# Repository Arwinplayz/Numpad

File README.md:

# Arwin's Numpad
A custom NumPad designed and built using **KiCad** for PCB design and **Fusion 360** for 3D modeling. This is my first hackpad project.

## Description
This project is a fully custom NumPad. The PCB and schematic are designed in KiCad, and the case and parts are modeled in Fusion 360. 

## Screenshots

### Overall Hackpad

### Schematic

### PCB Layout 

### Case

## Bill of Materials (BOM)
| Part | Quantity | Description |
|------|---------|-------------|
| Mechanical switches | 16 | Standard MX-compatible switches |
| Keycaps | 16 | Cherry-style keycaps |
| Xiao RP2040 | 1 | Microcontroller |
| 0.91 inch OLED Screen | 1 | Screen |
| Rotary Encoder | 2 | Dials |
| PCB | 1 | Custom-designed PCB |
| Screws / Standoffs | 8 | For case assembly |
| Heatset inserts| 8 | For case assembly |
| Case | 1 | 3D printed |

## Usage / Assembly
1. Fabricate the PCB according to the KiCad files.  
2. Solder everything onto the PCB.  
3. 3D Print the case and fit the PCB inside.  
4. Connect the microcontroller to your computer via USB and test functionality.

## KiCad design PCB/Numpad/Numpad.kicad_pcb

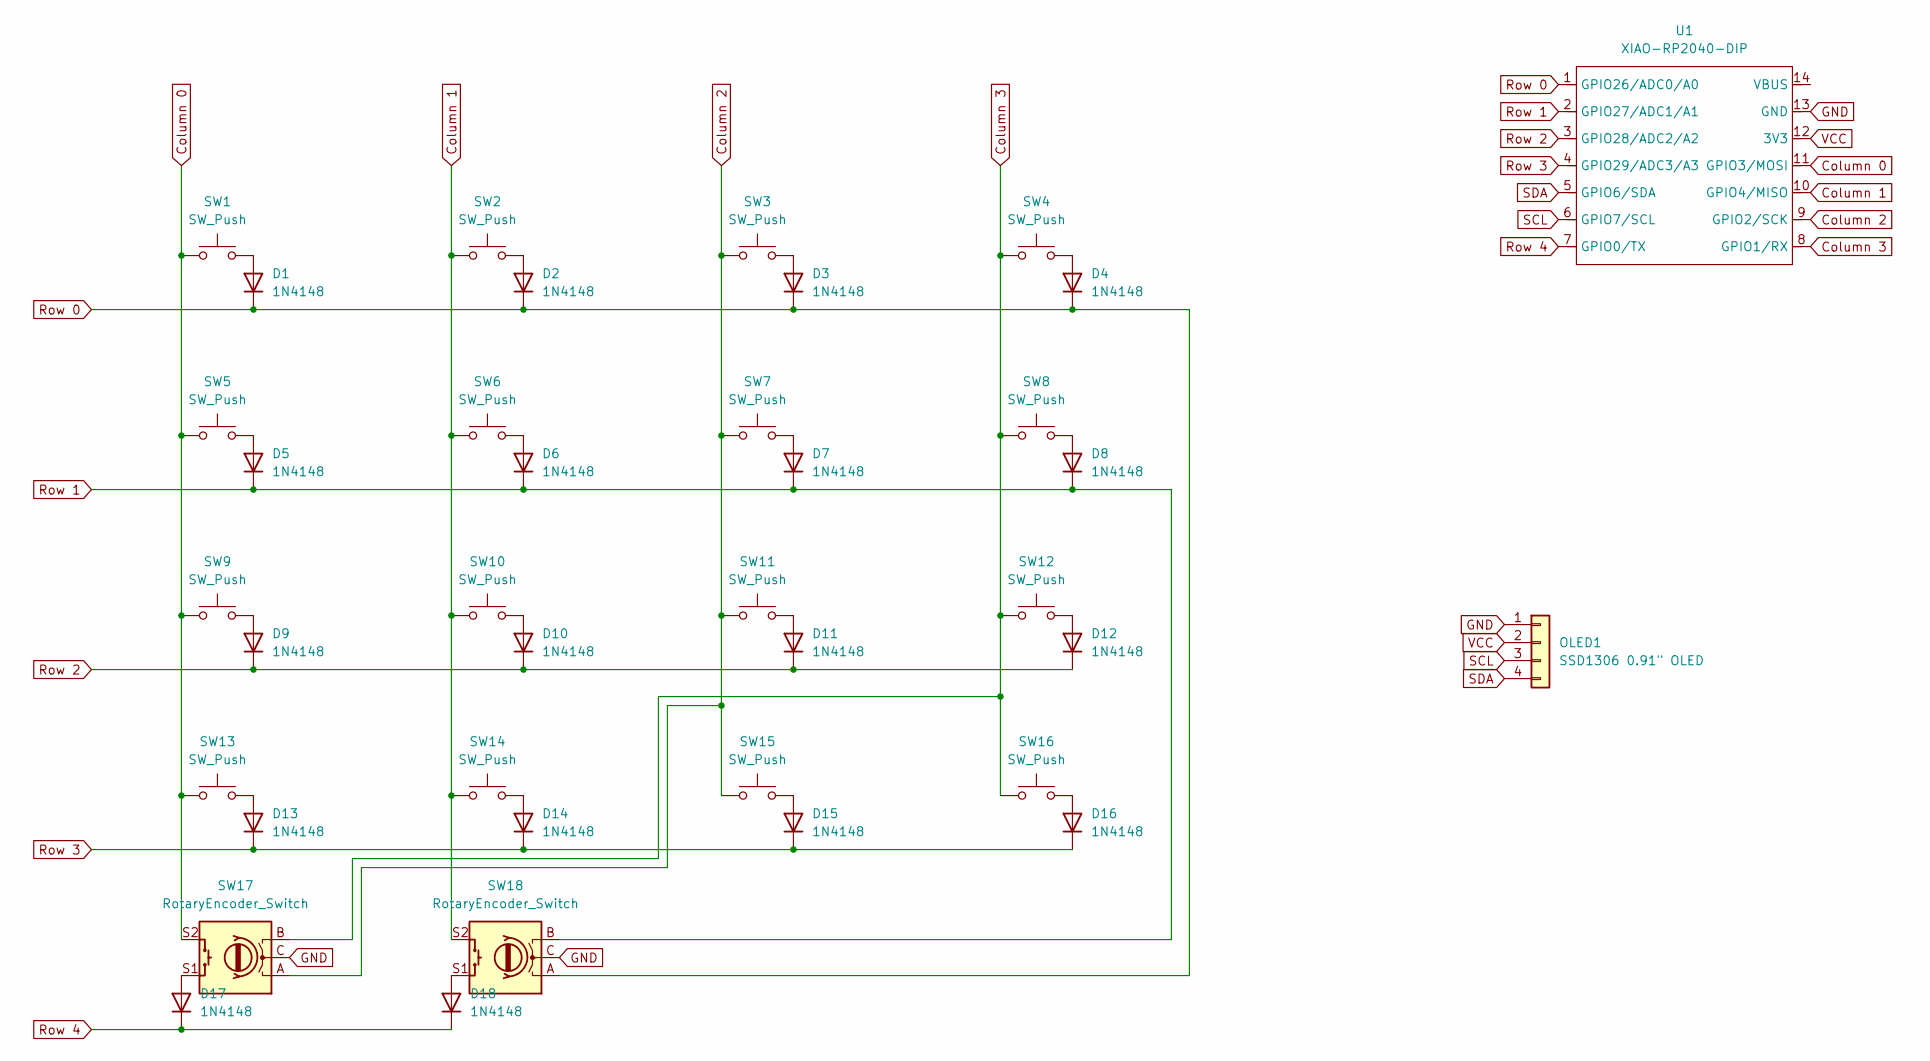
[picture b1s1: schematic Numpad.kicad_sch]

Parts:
D1, D2, D3, D4, D5, D6, D7, D8, D9, D10, D11, D12, D13, D14, D15, D16, D17, D18: 1N4148; D_DO-35_SOD27_P7.62mm_Horizontal
OLED1: SSD1306 0.91" OLED; SSD1306-0.91-OLED-4pin-128x32
SW1, SW2, SW3, SW4, SW5, SW6, SW7, SW8, SW9, SW10, SW11, SW12, SW13, SW14, SW15, SW16: SW_Push; SW_Cherry_MX_1.00u_PCB
SW17, SW18: RotaryEncoder_Switch; RotaryEncoder_Alps_EC11E-Switch_Vertical_H20mm
U1: XIAO-RP2040-DIP

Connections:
Column 0: SW1.1, SW5.1, SW9.1, SW13.1, SW17.S2, U1.11 (GPIO3/MOSI)
Column 1: SW2.1, SW6.1, SW10.1, SW14.1, SW18.S2, U1.10 (GPIO4/MISO)
Column 2: SW3.1, SW7.1, SW11.1, SW15.1, SW17.A, U1.9 (GPIO2/SCK)
Column 3: SW4.1, SW8.1, SW12.1, SW16.1, SW17.B, U1.8 (GPIO1/RX)
GND: OLED1.1, SW17.C, SW18.C, U1.13 (GND)
unnamed: D1.2 (A), SW1.2
unnamed: D2.2 (A), SW2.2
unnamed: D3.2 (A), SW3.2
unnamed: D4.2 (A), SW4.2
unnamed: D5.2 (A), SW5.2
unnamed: D6.2 (A), SW6.2
unnamed: D7.2 (A), SW7.2
unnamed: D8.2 (A), SW8.2
unnamed: D9.2 (A), SW9.2
unnamed: D10.2 (A), SW10.2
unnamed: D11.2 (A), SW11.2
unnamed: D12.2 (A), SW12.2
unnamed: D13.2 (A), SW13.2
unnamed: D14.2 (A), SW14.2
unnamed: D15.2 (A), SW15.2
unnamed: D16.2 (A), SW16.2
unnamed: D17.2 (A), SW17.S1
unnamed: D18.2 (A), SW18.S1
Row 0: D1.1 (K), D2.1 (K), D3.1 (K), D4.1 (K), SW18.A, U1.1 (GPIO26/ADC0/A0)
Row 1: D5.1 (K), D6.1 (K), D7.1 (K), D8.1 (K), SW18.B, U1.2 (GPIO27/ADC1/A1)
Row 2: D9.1 (K), D10.1 (K), D11.1 (K), D12.1 (K), U1.3 (GPIO28/ADC2/A2)
Row 3: D13.1 (K), D14.1 (K), D15.1 (K), D16.1 (K), U1.4 (GPIO29/ADC3/A3)
Row 4: D17.1 (K), D18.1 (K), U1.7 (GPIO0/TX)
SCL: OLED1.3, U1.6 (GPIO7/SCL)
SDA: OLED1.4, U1.5 (GPIO6/SDA)
VCC: OLED1.2, U1.12 (3V3)

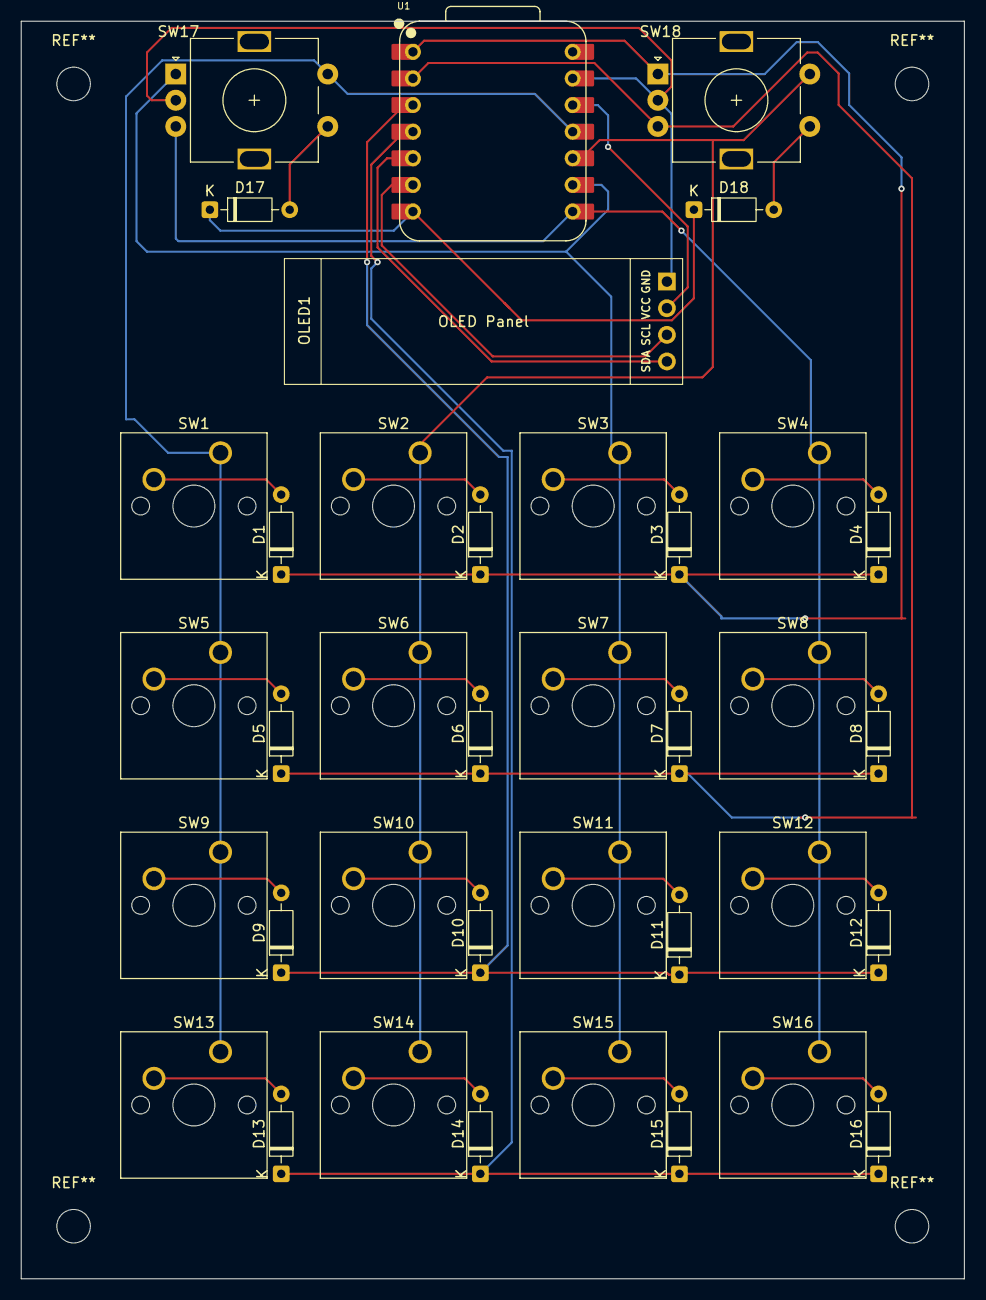
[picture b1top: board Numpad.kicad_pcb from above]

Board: 2 copper layers, 90.0 x 120.0 mm, 38 parts (0 on the bottom side), 31 nets.

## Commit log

2025-12-16 Added files for Numpad
2025-12-16 Update README and project files
